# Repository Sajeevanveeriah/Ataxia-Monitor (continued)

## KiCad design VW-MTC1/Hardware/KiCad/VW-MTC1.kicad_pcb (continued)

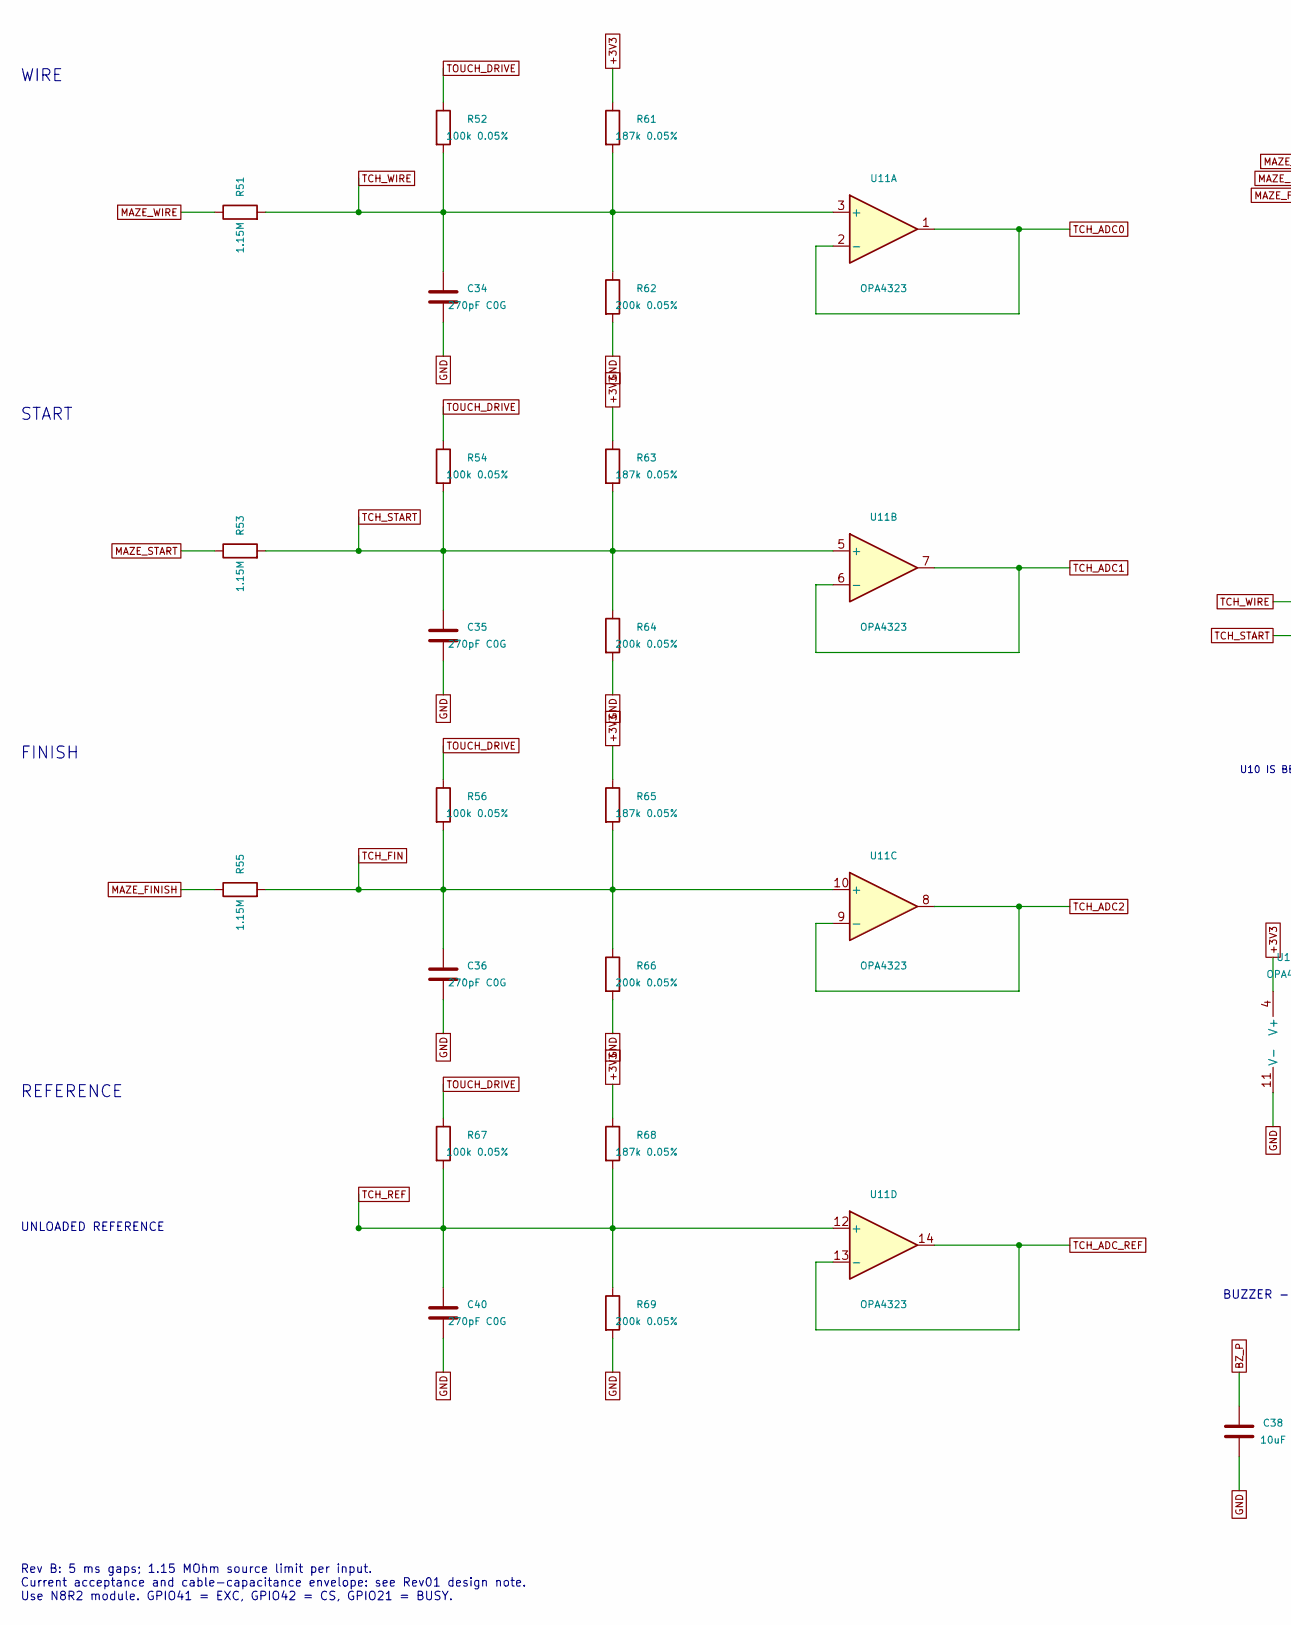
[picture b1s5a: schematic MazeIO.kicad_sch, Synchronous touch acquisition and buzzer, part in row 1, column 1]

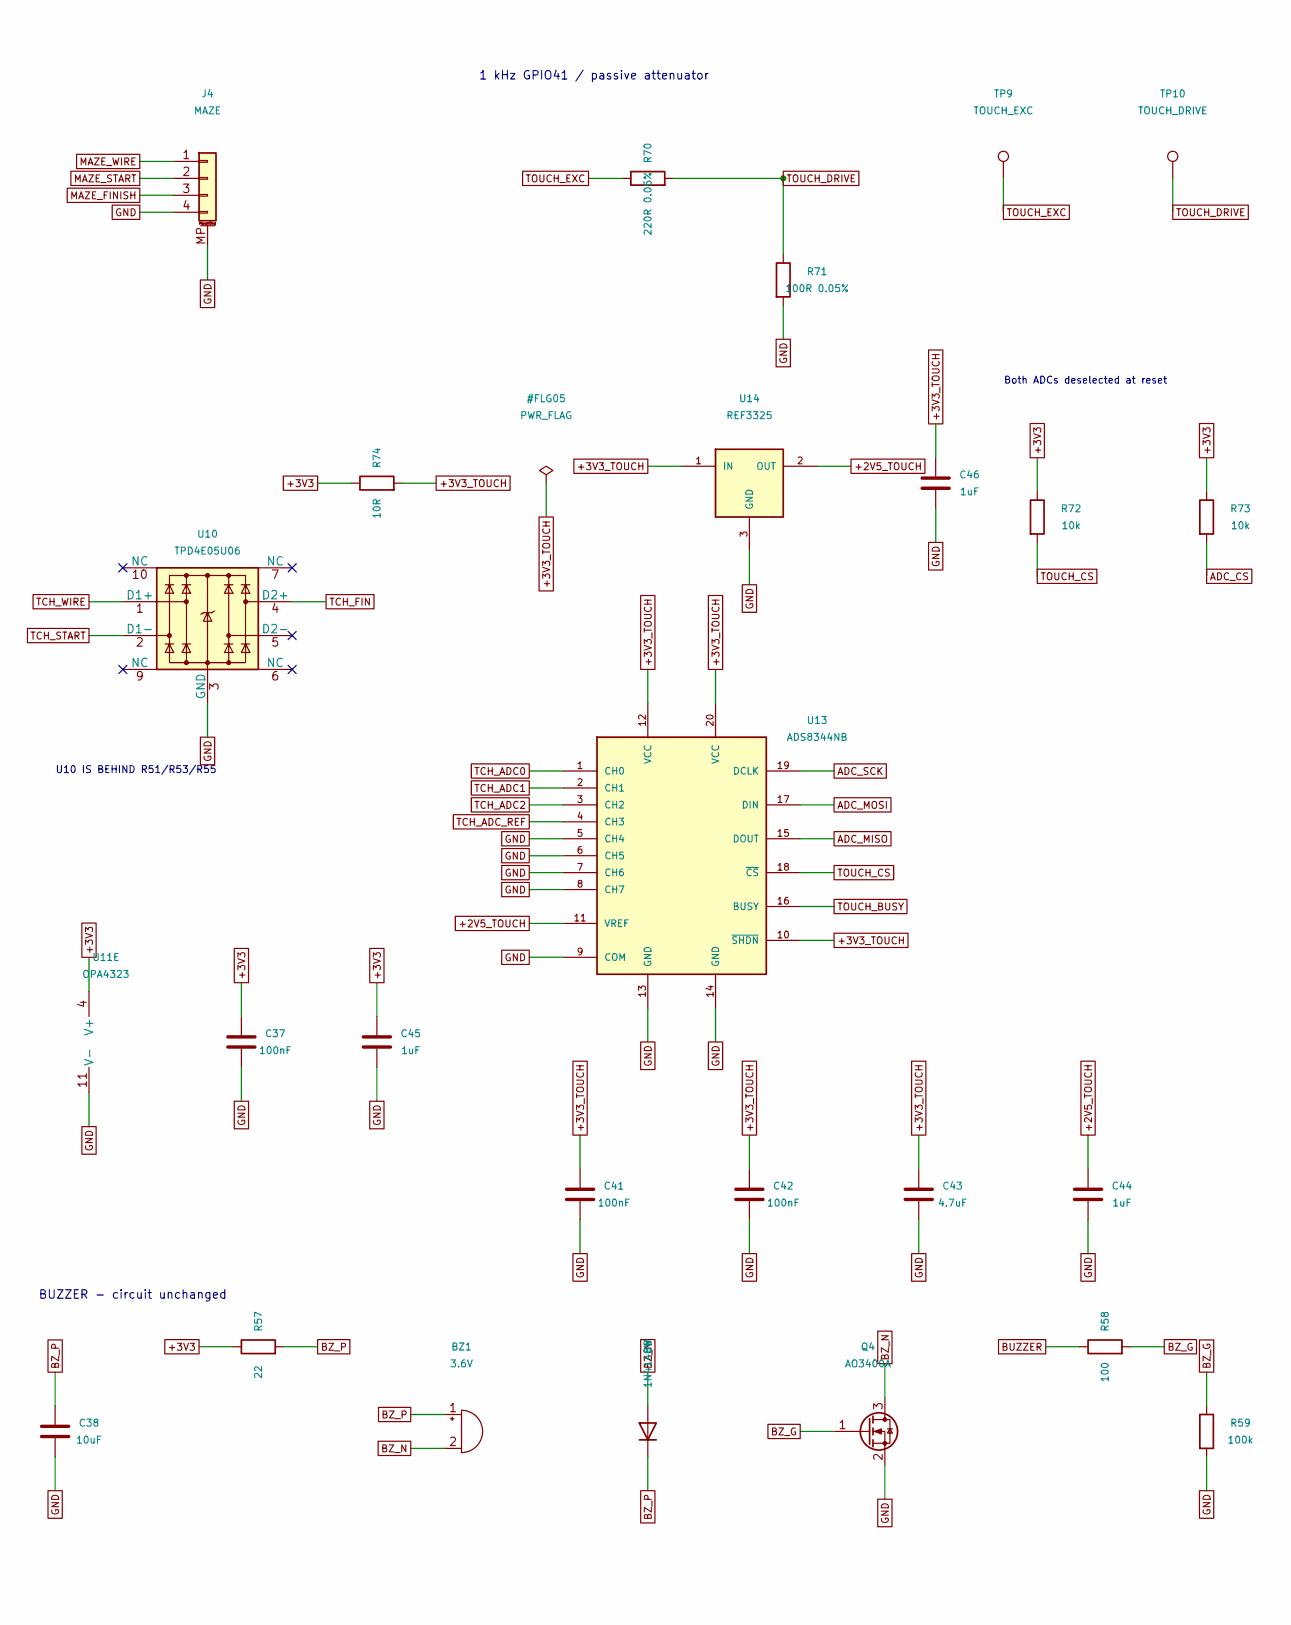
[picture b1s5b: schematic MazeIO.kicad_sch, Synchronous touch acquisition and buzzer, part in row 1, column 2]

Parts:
BZ1: 3.6V; MagneticBuzzer_CUI_CMT-8504-100-SMT; MPN CMT-8504-100-SMT-TR
C34, C35, C36, C40: 270pF C0G; C_0603_1608Metric; MPN GRM1885C1H271JA01D
C37, C41, C42: 100nF; C_0603_1608Metric; MPN GRM188R71H104KA93D
C38: 10uF; C_0805_2012Metric; MPN GRM21BR61E106KA73L
C43: 4.7uF; C_0603_1608Metric; MPN GRM188R60J475KE19D
C44, C45, C46: 1uF; C_0603_1608Metric; MPN GRM188R61E105KA12D
D8: 1N4148W; D_SOD-123; MPN 1N4148W-7-F
J4: MAZE; JST_PH_S4B-PH-SM4-TB_1x04-1MP_P2.00mm_Horizontal; MPN S4B-PH-SM4-TB(LF)(SN)
Q4: AO3400A; SOT-23; MPN AO3400A
R51, R53, R55: 1.15M; R_0603_1608Metric; MPN RC0603FR-071M15L
R52, R54, R56, R67: 100k 0.05%; R_0603_1608Metric; MPN RG1608N-104-W-T1
R57: 22; R_0805_2012Metric; MPN RC0805FR-0722RL
R58: 100; R_0603_1608Metric; MPN RC0603FR-07100L
R59: 100k; R_0603_1608Metric; MPN RC0603FR-07100kL
R61, R63, R65, R68: 187k 0.05%; R_0603_1608Metric; MPN RG1608N-1873-W-T1
R62, R64, R66, R69: 200k 0.05%; R_0603_1608Metric; MPN RG1608N-204-W-T1
R70: 220R 0.05%; R_0603_1608Metric; MPN RG1608N-221-W-T1
R71: 100R 0.05%; R_0603_1608Metric; MPN RG1608N-101-W-T1
R72, R73: 10k; R_0603_1608Metric; MPN RC0603FR-0710KL
R74: 10R; R_0603_1608Metric; MPN RC0603FR-0710RL
TP9: TOUCH_EXC; TestPoint_Pad_D1.5mm
TP10: TOUCH_DRIVE; TestPoint_Pad_D1.5mm
U10: TPD4E05U06; USON-10_2.5x1.0mm_P0.5mm; MPN TPD4E05U06DQAR
U11: OPA4323; TSSOP-14_4.4x5mm_P0.65mm; MPN OPA4323IPWR
U13: ADS8344NB; SSOP-20_5.3x7.2mm_P0.65mm; MPN ADS8344NB/1K
U14: REF3325; SOT-23; MPN REF3325AIDBZR

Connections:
+2V5_TOUCH: C44.1, U13.11 (VREF), U14.2 (OUT)
+3V3: C37.1, C45.1, R57.1, R61.1, R63.1, R65.1, R68.1, R72.1, R73.1, R74.1, U11.4 (V+); also elsewhere on the board
+3V3_TOUCH: C41.1, C42.1, C43.1, C46.1, R74.2, U13.10 (~SHDN), U13.12 (VCC), U13.20 (VCC), U14.1 (IN)
ADC_CS: R73.2; also elsewhere on the board
ADC_MISO: U13.15 (DOUT); also elsewhere on the board
ADC_MOSI: U13.17 (DIN); also elsewhere on the board
ADC_SCK: U13.19 (DCLK); also elsewhere on the board
BUZZER: R58.1; also elsewhere on the board
BZ_G: Q4.1 (G), R58.2, R59.1
BZ_N: BZ1.2 (-), D8.2 (A), Q4.3 (D)
BZ_P: BZ1.1 (+), C38.1, D8.1 (K), R57.2
GND: C34.2, C35.2, C36.2, C37.2, C38.2, C40.2, C41.2, C42.2, C43.2, C44.2, C45.2, C46.2, J4.4, J4.MP (MountPin), Q4.2 (S), R59.2, R62.2, R64.2, R66.2, R69.2, R71.2, U10.3 (GND), U10.8 (GND), U11.11 (V-), U13.5 (CH4), U13.6 (CH5), U13.7 (CH6), U13.8 (CH7), U13.9 (COM), U13.13 (GND), U13.14 (GND), U14.3 (GND); also elsewhere on the board
MAZE_FINISH: J4.3, R55.1
MAZE_START: J4.2, R53.1
MAZE_WIRE: J4.1, R51.1
TCH_ADC0: U11.1, U11.2 (-), U13.1 (CH0)
TCH_ADC1: U11.6 (-), U11.7, U13.2 (CH1)
TCH_ADC2: U11.8, U11.9 (-), U13.3 (CH2)
TCH_ADC_REF: U11.13 (-), U11.14, U13.4 (CH3)
TCH_FIN: C36.1, R55.2, R56.2, R65.2, R66.1, U10.4 (D2+), U11.10 (+)
TCH_REF: C40.1, R67.2, R68.2, R69.1, U11.12 (+)
TCH_START: C35.1, R53.2, R54.2, R63.2, R64.1, U10.2 (D1-), U11.5 (+)
TCH_WIRE: C34.1, R51.2, R52.2, R61.2, R62.1, U10.1 (D1+), U11.3 (+)
TOUCH_BUSY: U13.16 (BUSY); also elsewhere on the board
TOUCH_CS: R72.2, U13.18 (~CS); also elsewhere on the board
TOUCH_DRIVE: R52.1, R54.1, R56.1, R67.1, R70.2, R71.1, TP10.1
TOUCH_EXC: R70.1, TP9.1; also elsewhere on the board

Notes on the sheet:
WIRE
START
FINISH
UNLOADED REFERENCE
REFERENCE
U10 IS BEHIND R51/R53/R55
1 kHz GPIO41 / passive attenuator
Both ADCs deselected at reset
BUZZER - circuit unchanged
Rev B: 5 ms gaps; 1.15 MOhm source limit per input. Current acceptance and cable-capacitance envelope: see Rev01 design note. Use N8R2 module. GPIO41 = EXC, GPIO42 = CS, GPIO21 = BUSY.

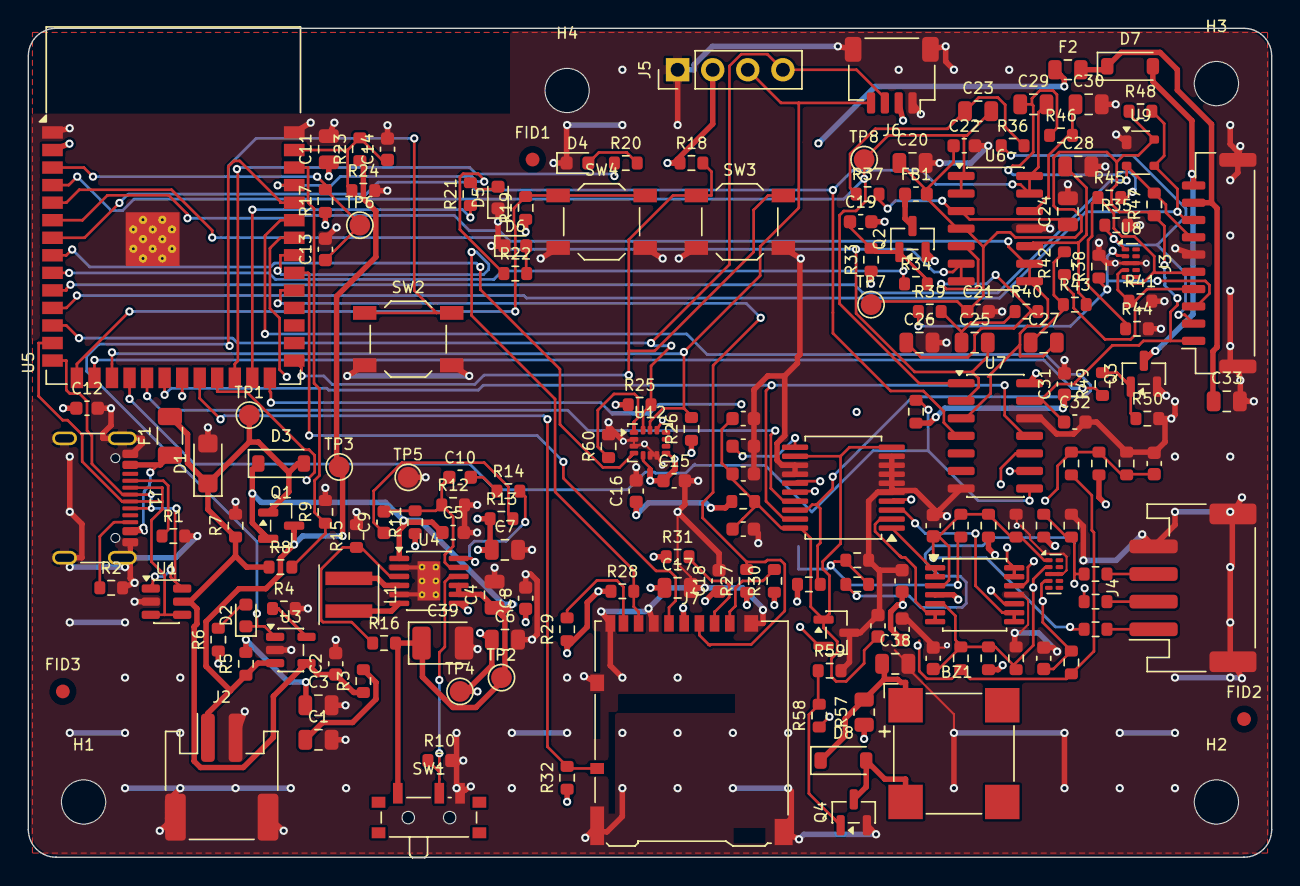
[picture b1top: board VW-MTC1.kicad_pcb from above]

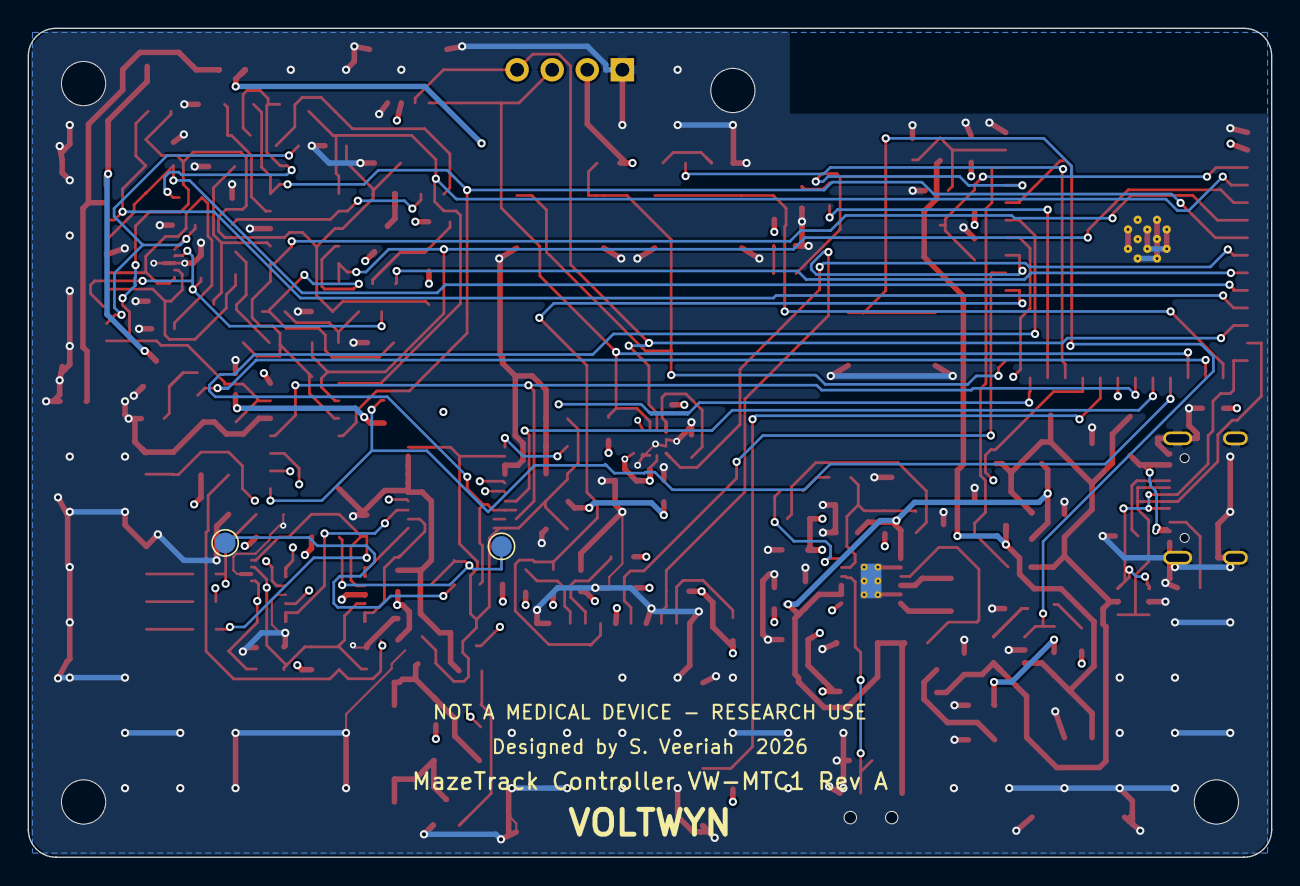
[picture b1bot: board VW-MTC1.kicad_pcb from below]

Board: 4 copper layers, 90.0 x 60.0 mm, 178 parts (2 on the bottom side), 96 nets.

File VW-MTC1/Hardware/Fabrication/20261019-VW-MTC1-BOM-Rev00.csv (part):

"Designator","Value","Footprint","MPN","Manufacturer","Description","Qty","DNP"
"BZ1","3.6V","Buzzer_Beeper:MagneticBuzzer_CUI_CMT-8504-100-SMT","CMT-8504-100-SMT-TR","CUI Devices","Magnetic transducer 3.6 V, external drive","1",""
"C1,C17,C20,C33,C38","10uF","Capacitor_SMD:C_0805_2012Metric","GRM21BR61E106KA73L","Murata","10 uF 25 V X5R 0805,Analog rail bulk,Buzzer reservoir (keeps pulses off +3V3),Motor local reservoir,SD card bulk","5",""
"C2,C13,C32","1uF","Capacitor_SMD:C_0603_1608Metric","GRM188R61E105KA12D","Murata","1 uF 25 V X5R 0603, charger VCC,ADC VREF bypass,EN power-on delay (Espressif guideline)","3",""
"C3","4.7uF","Capacitor_SMD:C_0805_2012Metric","GRM21BR61C475KA88L","Murata","4.7 uF 16 V X5R 0805","1",""
"C4,C6,C7,C11","22uF","Capacitor_SMD:C_0805_2012Metric","GRM21BR61A226ME44L","Murata","22 uF 10 V X5R 0805, buck-boost input,22 uF 10 V X5R 0805, output,22 uF module bulk","4",""
"C5,C8,C12,C14,C15,C16,C18,C21,C22,C31,C37","100nF","Capacitor_SMD:C_0603_1608Metric","GRM188R71H104KA93D","Murata","100 nF 50 V X7R 0603,100 nF module bypass,100 nF output HF bypass,ADC VDD bypass,ADC charge reservoir,Analog rail bypass,IMU VDD bypass,IMU VDDIO bypass,Op-amp bypass,SD card bypass,Schmitt buffer bypass","11",""
"C9","47pF","Capacitor_SMD:C_0603_1608Metric","GRM1885C1H470JA01D","Murata","47 pF C0G feed-forward","1",""
"C10","220pF","Capacitor_SMD:C_0603_1608Metric","GRM1885C1H221JA01D","Murata","220 pF C0G compensation","1",""
"C19","47nF","Capacitor_SMD:C_0603_1608Metric","GRM188R71H473KA61D","Murata","Gate slew cap, limits inrush","1",""
"C23,C25,C27,C29","100nF","Capacitor_SMD:C_0805_2012Metric","GCM21B5C1H104JA16L","Murata","100 nF C0G 0805, Sallen-Key feedback","4",""
"C24,C26,C28,C30","47nF","Capacitor_SMD:C_0805_2012Metric","GRM2195C1H473JA01D","Murata","47 nF C0G 0805, Sallen-Key shunt","4",""
"C34,C35,C36","27nF","Capacitor_SMD:C_0603_1608Metric","GRM188R71H273KA01D","Murata","Mains-hum filter, 100 pF coupling immune (SIM05)","3",""
"C39","100uF","Capacitor_Tantalum_SMD:CP_EIA-3528-21_Kemet-B","T520B107M006ATE070","KEMET","100 uF 6.3 V polymer tantalum, 70 mohm ESR, VSYS hold-up on USB replug (SIM03)","1",""
"D1","SMF5V0A","Diode_SMD:D_SMF","SMF5V0A","Littelfuse","TVS 5 V standoff, 200 W, VBUS surge clamp","1",""
"D2,D5","RED","LED_SMD:LED_0603_1608Metric","150060RS75000","Wurth","Red LED 0603, charging indicator,Red LED 0603, reverse","2",""
"D3,D7","B5819W","Diode_SMD:D_SOD-123","B5819W","Diodes Inc","Motor flyback clamp,Schottky 40 V 1 A, USB to VSYS OR-ing","2",""
"D4","GREEN","LED_SMD:LED_0603_1608Metric","150060GS75000","Wurth","Green LED 0603, forward","1",""
"D6","AMBER","LED_SMD:LED_0603_1608Metric","150060AS75000","Wurth","Amber LED 0603, idle","1",""
"D8","1N4148W","Diode_SMD:D_SOD-123","1N4148W-7-F","Diodes Inc","Buzzer coil flyback","1",""
"F1","0.75A","Fuse:Fuse_1206_3216Metric","1206L075THYR","Littelfuse","PTC resettable fuse 0.75 A hold, 6 V","1",""
"F2","0.2A","Fuse:Fuse_0805_2012Metric","0805L020WR","Littelfuse","PTC 0.2 A hold, protects VSYS from cable faults","1",""
"FB1","600R@100MHz","Inductor_SMD:L_0603_1608Metric","BLM18PG601SN1D","Murata","Ferrite bead 600 R @ 100 MHz, 500 mA","1",""
"J1","USB-C","Connector_USB:USB_C_Receptacle_GCT_USB4105-xx-A_16P_TopMnt_Horizontal","USB4105-GF-A","GCT","USB Type-C receptacle, USB 2.0, 16P","1",""
"J2","BATT 1S","Connector_JST:JST_PH_S2B-PH-SM4-TB_1x02-1MP_P2.00mm_Horizontal","S2B-PH-SM4-TB(LF)(SN)","JST","1S Li-ion/LiPo battery connector (protected cell required)","1",""
"J3","HANDLE","Connector_JST:JST_GH_SM10B-GHS-TB_1x10-1MP_P1.25mm_Horizontal","SM10B-GHS-TB(LF)(SN)","JST","Handle cable: 4x SS49E, I2C, haptic motor, ring = GND","1",""
"J4","MAZE","Connector_JST:JST_PH_S4B-PH-SM4-TB_1x04-1MP_P2.00mm_Horizontal","S4B-PH-SM4-TB(LF)(SN)","JST","Maze wire, start pad, finish pad, ground","1",""
"J5","OLED","Connector_PinHeader_2.54mm:PinHeader_1x04_P2.54mm_Vertical","PH1-04-UA","Adam Tech","SSD1306 0.96/1.3 inch OLED header (GND VCC SCL SDA)","1",""
"J6","QWIIC","Connector_JST:JST_SH_SM04B-SRSS-TB_1x04-1MP_P1.00mm_Horizontal","SM04B-SRSS-TB(LF)(SN)","JST","Qwiic/STEMMA QT I2C expansion (e.g. VL53L1X LiDAR)","1",""
"J7","microSD","Connector_Card:microSD_HC_Hirose_DM3AT-SF-PEJM5","DM3AT-SF-PEJM5","Hirose","microSD push-push socket with card detect","1",""
"L1","4.7uH","Inductor_SMD:L_Coilcraft_XxL4020","XFL4020-472MEC","Coilcraft","4.7 uH 2.7 A shielded power inductor","1",""
"Q1,Q2","AO3401A","Package_TO_SOT_SMD:SOT-23","AO3401A","Alpha & Omega","Hall sensor rail switch (power down between sessions),P-MOSFET -30 V, battery load-sharing switch","2",""
"Q3,Q4","AO3400A","Package_TO_SOT_SMD:SOT-23","AO3400A","Alpha & Omega","Buzzer low-side switch,N-MOSFET 30 V, haptic motor low-side switch","2",""
"R1,R2","5.1k","Resistor_SMD:R_0603_1608Metric","RC0603FR-075R1kL","Yageo","CC1 Rd pull-down (UFP, default USB current),CC2 Rd pull-down","2",""
"R3","1.5","Resistor_SMD:R_0603_1608Metric","RC0603FR-071R5L","Yageo","Hot-plug damping resistor (LTC4054 app note)","1",""
"R4","2.49k","Resistor_SMD:R_0603_1608Metric","RC0603FR-072K49L","Yageo","Charge current 1000 x 1 V / 2.49k = 402 mA","1",""
"R5","1","Resistor_SMD:R_0603_1608Metric","RC0603FR-071RL","Yageo","Series R for ceramic BAT cap (LTC4054 stability)","1",""
"R6","1k","Resistor_SMD:R_0603_1608Metric","RC0603FR-071kL","Yageo","Charge LED current limit","1",""
"R7,R47,R48","2.2k","Resistor_SMD:R_0603_1608Metric","RC0603FR-072R2kL","Yageo","Handle I2C pull-up,Handle I2C pull-up (cable capacitance),Q1 gate pull-down: discharges VBUS so Q1 turns on within ~5.5 ms of unplug (SIM03)","3",""
"R8,R9,R16,R33,R50,R59","100k","Resistor_SMD:R_0603_1608Metric","RC0603FR-07100kL","Yageo","Gate pull-down (motor off at boot),Gate pull-down (silent at boot),MODE strap option: fit (and remove R15) for Burst Mode,Q2 default off,USB detect divider bottom,USB detect divider top","6","DNP"
"R10,R11,R23,R24,R35,R38,R41,R44","1M","Resistor_SMD:R_0603_1608Metric","RC0603FR-071ML","Yageo","Battery divider bottom,Battery divider top (2 uA drain),Enable defined low during switch travel,Feedback top (VOUT = 0.6 x (1 + 1M/221k) = 3.315 V),Handle-absent detect pull-down","8",""
"R12","221k","Resistor_SMD:R_0603_1608Metric","RC0603FR-07221kL","Yageo","Feedback bottom","1",""
"R13","6.49k","Resistor_SMD:R_0603_1608Metric","RC0603FR-076R49kL","Yageo","Feed-forward zero resistor","1",""
"R14","49.9k","Resistor_SMD:R_0603_1608Metric","RC0603FR-0749R9kL","Yageo","Compensation resistor","1",""
"R15","0","Resistor_SMD:R_0603_1608Metric","RC0603JR-070RL","Yageo","MODE strap: fitted = fixed-frequency PWM (lowest noise)","1",""
"R17,R18,R19,R27,R28,R29,R30,R31,R32,R36,R37,R39,R40,R42,R43,R45,R46,R51,R53,R55,R60","10k","Resistor_SMD:R_0603_1608Metric","RC0603FR-0710kL","Yageo","Button pull-up,EN pull-up,GPIO0 strap pull-up,IMU address strap SA0=0 (0x6A); move to +3V3 for 0x6B,SD bus pull-up,Sallen-Key R1,Sallen-Key R2,Series R (SIM05 revised)","21",""
"R20,R21,R22","470","Resistor_SMD:R_0603_1608Metric","RC0603FR-07470L","Yageo","LED current ~2.5 mA","3",""
"R25,R26,R34","4.7k","Resistor_SMD:R_0603_1608Metric","RC0603FR-074R7kL","Yageo","Gate series R, soft start with C19,I2C0 pull-up","3",""
"R49,R58","100","Resistor_SMD:R_0603_1608Metric","RC0603FR-07100L","Yageo","Gate series R","2",""
"R52,R54,R56","360k","Resistor_SMD:R_0603_1608Metric","RC0603FR-07360kL","Yageo","Touch pull-up: limits current through a person to 9 uA (SIM05)","3",""
"R57","22","Resistor_SMD:R_0805_2012Metric","RC0805FR-0722RL","Yageo","Buzzer current limit 0805","1",""
"SW1","POWER","Button_Switch_SMD:SW_SPDT_PCM12","PCM12SMTR","C&K","Slide switch SPDT, power on/off (regulator enable)","1",""
"SW2","RESET","Button_Switch_SMD:SW_SPST_TL3342","TL3342F160QG","E-Switch","Tactile switch, reset","1",""
"SW3","BOOT/MODE","Button_Switch_SMD:SW_SPST_TL3342","TL3342F160QG","E-Switch","Tactile switch, boot / user mode","1",""
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
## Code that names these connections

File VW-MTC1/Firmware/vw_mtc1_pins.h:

// VW-MTC1 MazeTrack Controller - Rev B - ESP32-S3-WROOM-1 (N8R2) pin map
// Source of truth: Hardware/KiCad schematic (MCU and MazeIO sheets).
// Rev B touch firmware MUST NOT be flashed onto an unmodified Rev A board.
// Module variant: use N8 / N8R2 (quad PSRAM). Octal-PSRAM variants (R8) reserve GPIO35-37,
// which this board leaves unconnected anyway.
#pragma once

// ---- Hall sensor front end (4 x SS49E in the handle) ----
// Primary path: MCP3204 12-bit ADC on SPI, VREF = +3V3_H (ratiometric with the sensors)
#define PIN_ADC_CS        10   // MCP3204 CS/SHDN (active low)
#define PIN_ADC_MOSI      11   // MCP3204 DIN
#define PIN_ADC_SCK       12   // MCP3204 CLK, run at 1 MHz
#define PIN_ADC_MISO      13   // MCP3204 DOUT
// Backup path: same filtered signals on ESP32-S3 ADC1 (lite build can omit U7)
#define PIN_HALL_F1        4   // ADC1_CH3
#define PIN_HALL_F2        5   // ADC1_CH4
#define PIN_HALL_F3        6   // ADC1_CH5
#define PIN_HALL_F4        7   // ADC1_CH6
#define PIN_HALL_EN_N     16   // LOW = handle sensors + op-amp powered (Q2). Default off (pull-up).

// ---- Handle I2C (I2C1, 2.2k pull-ups to +3V3_H; powered only when HALL_EN_N is LOW) ----
#define PIN_SDA_H         17
#define PIN_SCL_H         18

// ---- On-board I2C (I2C0): OLED (0x3C), ISM330DHCX IMU (0x6A), Qwiic expansion ----
#define PIN_SDA            8
#define PIN_SCL            9
#define PIN_IMU_INT1      15

// ---- Rev B synchronous touch acquisition (ADS8344NB on shared SPI) ----
#define PIN_TOUCH_EXC     41   // 1 kHz hardware carrier, 50% duty
#define PIN_TOUCH_CS      42   // ADS8344NB chip select, active LOW
#define PIN_TOUCH_BUSY    21   // ADS8344NB BUSY, diagnostic input
// CH0 = wire, CH1 = start, CH2 = finish, CH3 = unloaded reference.
// These are analogue measurements; GPIO levels are not contact states.

// ---- microSD (SDMMC 1-bit mode; D1-D3 pulled up) ----
#define PIN_SD_CLK        39
#define PIN_SD_CMD        38
#define PIN_SD_D0         40
#define PIN_SD_CD         14   // LOW = card inserted

// ---- User interface ----
#define PIN_BTN_START      3   // LOW = pressed (10k pull-up)
#define PIN_BTN_MODE       0   // BOOT strap; usable as MODE button after boot
#define PIN_LED_GREEN     47   // forward (active HIGH)
#define PIN_LED_RED       48   // reverse (active HIGH)
#define PIN_LED_AMBER     43   // idle (active HIGH; flickers with U0TXD boot log)
#define PIN_BUZZER        45   // magnetic transducer, drive ~4 kHz PWM (strap pin: keep LOW at boot)
#define PIN_HAPTIC_PWM    46   // ERM motor in handle, 20 kHz PWM (strap pin: pulled LOW)

// ---- Power monitoring ----
#define PIN_VBAT_SENSE     1   // VBAT / 2 (1M/1M + 100 nF). VBAT = 2 * Vadc
#define PIN_VBUS_SENSE     2   // VBUS / 2 when USB present
#define PIN_CHRG_N        44   // LOW = charging (LTC4054 CHRG; enable internal pull-up)

// ---- Native USB (CDC + JTAG) ----
// GPIO19 = USB_D-, GPIO20 = USB_D+

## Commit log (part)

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2025-10-11 Add Android app for ataxia sensor monitoring
